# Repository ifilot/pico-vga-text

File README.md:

# PicoBeam: A Raspberry Pi Pico 2 based VGA Display

This project demonstrates how to drive a VGA display using the **Raspberry Pi
Pico 2**. The display uses a 640x480 pixel resolution with 16 colors (4-bit
color depth). The Raspberry Pi Pico communicates with the display via a single
8-bit interface latch and provides debugging via UART.

## Features

- **Resolution**: 640 x 480 pixels
- **Builtin Font**: Original Philips P2000C 12x8 bitmap font
- **Bitmapped graphics**: Support for printing individual pixels to the screen
- **Color Depth**: 4-bit (16 colors)
- **Refresh Rate**: ~72 Hz (using a 150 MHz clock with a x5 clock divider)
- **Interface**: Single 8-bit latch for display control
- **UART**: For debugging and communication
- **Beeper**: 1-bit beeper for simple audio feedback

> [!WARNING]
> **Do not connect this board to a CRT monitor unless you are absolutely sure
> that the monitor supports 72 Hz vertical sync at 640x480 resolution**. 
> Connecting this board to a CRT that does not support these specifications may
> cause **damage to the monitor** or result in **display instability**. 
> Always check your CRT monitor's specifications to confirm compatibility with
> 72 Hz VSync at 640x480 resolution before proceeding.

## How It Works

The Raspberry Pi Pico drives the display by receiving pixel data through an
8-bit latch interface, which updates the screen in real-time. By connecting
the Pico to the data bus of a CPU or microcontroller, instructions can be sent
to the Pico.

## Compilation instructions

### Toolchain

```bash
sudo apt install cmake gcc-arm-none-eabi libnewlib-arm-none-eabi build-essential libstdc++-arm-none-eabi-newlib
sudo git clone https://github.com/raspberrypi/pico-sdk.git /opt/pico-sdk
sudo git -C /opt/pico-sdk submodule update --init
RUN 'export PICO_SDK_PATH=/opt/pico-sdk' | tee -a /etc/profile.d/pico-sdk.sh
```

### Compiling

```bash
mkdir build && cd build
cmake ../src
make -j
```

## Instruction delays

The Pico requires a bit of processing time and one should be cautious not to
sent the data too fast. The following timings were found to give stable results
when using a simple (slow) voltage divider circuit. When connecting the Pico to
your specific setup, it is recommended to perform your own calibration to find
which delays provide stable results.

| Operation                                         | Delay (μs) |
|---------------------------------------------------|------------|
| Single characters                                 | 150        |
| Large instructions (e.g., beeper or screen clear) | 2000       |

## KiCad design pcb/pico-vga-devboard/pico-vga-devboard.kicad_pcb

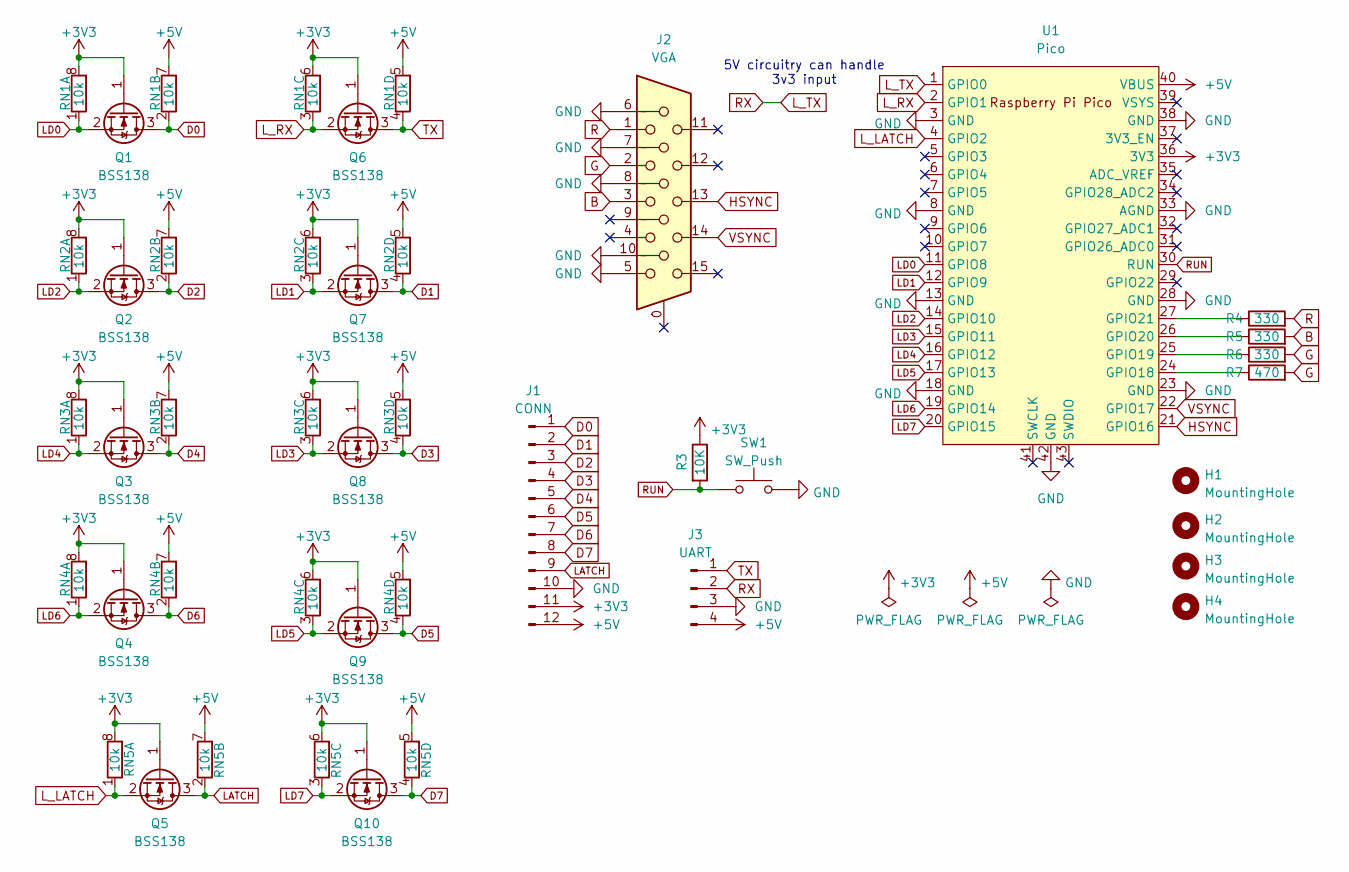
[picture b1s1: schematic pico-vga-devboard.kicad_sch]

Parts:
H1, H2, H3, H4: MountingHole; MountingHole_3.2mm_M3
J1: CONN; PinHeader_1x12_P2.54mm_Vertical
J2: VGA; 618015330923
J3: UART; PinHeader_1x04_P2.54mm_Vertical
Q1, Q2, Q3, Q4, Q5, Q6, Q7, Q8, Q9, Q10: BSS138; SOT-23; LCSC C78284
R3: 10K; R_0805_2012Metric_Pad1.20x1.40mm_HandSolder; LCSC C17414
R4, R5, R6: 330; R_0805_2012Metric_Pad1.20x1.40mm_HandSolder; LCSC C17630
R7: 470; R_0805_2012Metric_Pad1.20x1.40mm_HandSolder; LCSC C17710
RN1, RN2, RN3, RN4, RN5: 10k; R_Array_Convex_4x0603; LCSC C110924
SW1: SW_Push; SW_PUSH_6mm
U1: Pico; RPi_Pico_SMD_TH

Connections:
+3V3: J1.11, Q1.1 (G), Q2.1 (G), Q3.1 (G), Q4.1 (G), Q5.1 (G), Q6.1 (G), Q7.1 (G), Q8.1 (G), Q9.1 (G), Q10.1 (G), R3.1, RN1.6 (R3.2), RN1.8 (R1.2), RN2.6 (R3.2), RN2.8 (R1.2), RN3.6 (R3.2), RN3.8 (R1.2), RN4.6 (R3.2), RN4.8 (R1.2), RN5.6 (R3.2), RN5.8 (R1.2), U1.36 (3V3)
+5V: J1.12, J3.4, RN1.5 (R4.2), RN1.7 (R2.2), RN2.5 (R4.2), RN2.7 (R2.2), RN3.5 (R4.2), RN3.7 (R2.2), RN4.5 (R4.2), RN4.7 (R2.2), RN5.5 (R4.2), RN5.7 (R2.2), U1.40 (VBUS)
B: J2.3, R5.2
D0: J1.1, Q1.3 (D), RN1.2 (R2.1)
D1: J1.2, Q7.3 (D), RN2.4 (R4.1)
D2: J1.3, Q2.3 (D), RN2.2 (R2.1)
D3: J1.4, Q8.3 (D), RN3.4 (R4.1)
D4: J1.5, Q3.3 (D), RN3.2 (R2.1)
D5: J1.6, Q9.3 (D), RN4.4 (R4.1)
D6: J1.7, Q4.3 (D), RN4.2 (R2.1)
D7: J1.8, Q10.3 (D), RN5.4 (R4.1)
G: J2.2, R6.2, R7.2
GND: J1.10, J2.5, J2.6, J2.7, J2.8, J2.10, J3.3, SW1.2, U1.3 (GND), U1.8 (GND), U1.13 (GND), U1.18 (GND), U1.23 (GND), U1.28 (GND), U1.33 (AGND), U1.38 (GND), U1.42 (GND)
HSYNC: J2.13, U1.21 (GPIO16)
LATCH: J1.9, Q5.3 (D), RN5.2 (R2.1)
LD0: Q1.2 (S), RN1.1 (R1.1), U1.11 (GPIO8)
LD1: Q7.2 (S), RN2.3 (R3.1), U1.12 (GPIO9)
LD2: Q2.2 (S), RN2.1 (R1.1), U1.14 (GPIO10)
LD3: Q8.2 (S), RN3.3 (R3.1), U1.15 (GPIO11)
LD4: Q3.2 (S), RN3.1 (R1.1), U1.16 (GPIO12)
LD5: Q9.2 (S), RN4.3 (R3.1), U1.17 (GPIO13)
LD6: Q4.2 (S), RN4.1 (R1.1), U1.19 (GPIO14)
LD7: Q10.2 (S), RN5.3 (R3.1), U1.20 (GPIO15)
L_LATCH: Q5.2 (S), RN5.1 (R1.1), U1.4 (GPIO2)
L_RX: Q6.2 (S), RN1.3 (R3.1), U1.2 (GPIO1)
L_TX: J3.2, U1.1 (GPIO0)
unnamed: R7.1, U1.24 (GPIO18)
unnamed: R6.1, U1.25 (GPIO19)
unnamed: R5.1, U1.26 (GPIO20)
unnamed: R4.1, U1.27 (GPIO21)
R: J2.1, R4.2
RUN: R3.2, SW1.1, U1.30 (RUN)
TX: J3.1, Q6.3 (D), RN1.4 (R4.1)
VSYNC: J2.14, U1.22 (GPIO17)

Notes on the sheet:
5V circuitry can handle 3v3 input

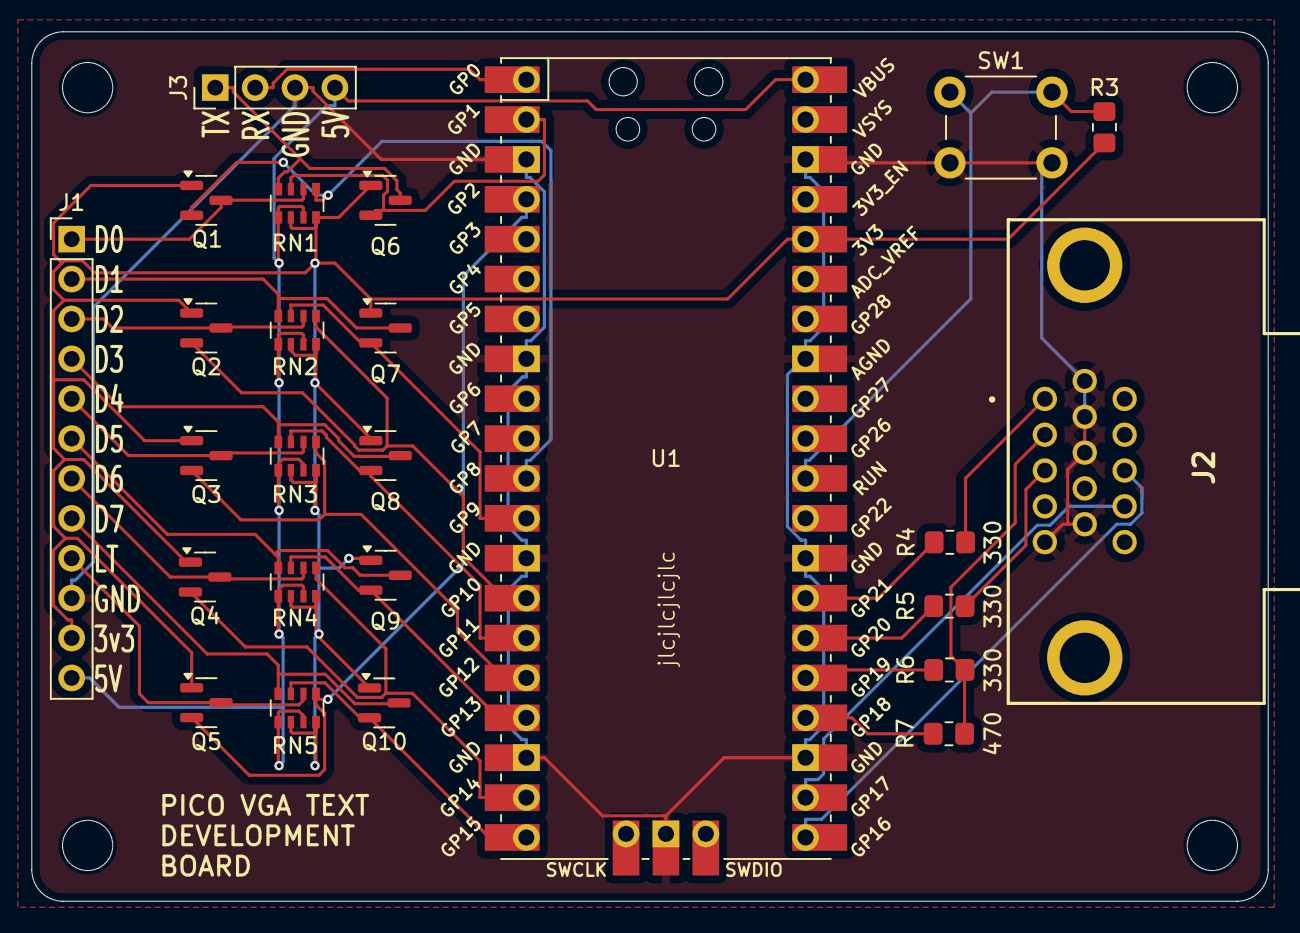
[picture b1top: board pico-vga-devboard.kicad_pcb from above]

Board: 2 copper layers, 78.7 x 55.4 mm, 29 parts (0 on the bottom side), 34 nets.

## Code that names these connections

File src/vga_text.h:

/**
 *
 * HARDWARE CONNECTIONS
 *  - GPIO 16 ---> VGA Hsync
 *  - GPIO 17 ---> VGA Vsync
 *  - GPIO 18 ---> 470 ohm resistor ---> VGA Green 
 *  - GPIO 19 ---> 330 ohm resistor ---> VGA Green
 *  - GPIO 20 ---> 330 ohm resistor ---> VGA Blue
 *  - GPIO 21 ---> 330 ohm resistor ---> VGA Red
 *  - RP2040 GND ---> VGA GND
 *
 * RESOURCES USED
 *  - PIO state machines 0, 1, and 2 on PIO instance 0
 *  - DMA channels 0, 1, 2, and 3
 *  - 153.6 kBytes of RAM (for pixel color data)
 *
 */

#ifndef _VGA_TEXT_H
#define _VGA_TEXT_H

#include <stdio.h>
#include <stdlib.h>
#include <string.h>
#include <pico/stdlib.h>
#include <hardware/pio.h>
#include <hardware/dma.h>

#include "hsync.pio.h"
#include "vsync.pio.h"
#include "rgb.pio.h"

// Screen width/height
#define SCREENWIDTH     640     // width of the screen
#define SCREENHEIGHT    480     // height of the screen
#define CHARHEIGHT      12      // character width
#define CHARWIDTH        8      // character height

#define LATCH_PIN 2         // GPIO for latch signal
#define DATA_BASE_PIN 8     // First data pin

// VGA timing constants
#define H_ACTIVE 655   // (active + frontporch - 1) - one cycle delay for mov
#define V_ACTIVE 479   // (active - 1)
#define RGB_ACTIVE 319 // (horizontal active)/2 - 1
// #define RGB_ACTIVE 639 // change to this if 1 pixel/byte

// Length of the pixel array, and number of DMA transfers
#define TXCOUNT 153600 // Total pixels/2 (since we have 2 pixels per byte)

// Give the I/O pins that we're using some names that make sense - usable in
// main()
enum vga_pins {HSYNC=16, VSYNC, LO_GRN, HI_GRN, BLUE_PIN, RED_PIN} ;

// We can only produce 16 (4-bit) colors, so let's give them readable names -
// usable in main()
enum colors {BLACK, DARK_GREEN, MED_GREEN, GREEN,
             DARK_BLUE, BLUE, LIGHT_BLUE, CYAN,
             RED, DARK_ORANGE, ORANGE, YELLOW, 
             MAGENTA, PINK, LIGHT_PINK, WHITE} ;

// Bit masks for drawPixel routine
#define TOPMASK 0b00001111
#define BOTTOMMASK 0b11110000

// For writing text
#define tabspace 4 // number of spaces for a tab

// For accessing the font library
#define pgm_read_byte(addr) (*(const unsigned char *)(addr))

extern bool flag_beep;
extern bool flag_beeping;

/**
 * @brief Initialize the screen
 * 
 */
void init_screen(void) ;

/**
 * @brief Clear the screen
 * 
 */
void clear_screen();

/**
 * @brief Draw a single pixel to thes creen buffer
 * 
 * @param x         Pixel x-coordinate
 * @param y         Pixel y-coordinate
 * @param color     Pixel color
 * 
 * 
 * This function modifies the contents of the VGA data array, which is
 * automatically transferred to the screen via a DMA channel.
 */
void draw_pixel(short x, short y, char color) ;

/**
 * @brief Draw a character onto the screen
 * 
 * @param x         Character x-position
 * @param y         Character y-position
 * @param c         Character to print
 * @param color     Foreground color
 * @param bg        Background color
 */
void draw_character(short x, short y, unsigned char c, char color, char bg) ;

#endif // _VGA_TEXT_H

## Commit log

2025-03-07 Fixing font layout to 12x8
2025-03-07 Integrating 8-bit latch
2025-03-07 Implementing control characters for color swaps
2025-03-07 Adding development board
2025-03-07 Adding README and tweaking comments
2025-03-07 Adding font info
2025-03-07 Adding buzzer and refactoring code
2025-03-08 Adding Github actions
2025-03-08 Adding comments
2025-03-08 Adding compilation procedure
2025-03-08 Fixing name
2025-03-08 Changing names
2025-03-08 Integrating drawing pixels

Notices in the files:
README.md:
License: GPL v3
License: CC BY-SA 4.0
